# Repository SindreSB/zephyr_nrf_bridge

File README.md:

# Zephyr based bridge for Dexcom G4

Highly WIP, and not at all working

## Installation
This repo contains a west manifest file, which enables this to be a manifest repo when using the west tool.

Steps to get up and running:
1. Follow install guide for zephyr/west
1. Clone this repo 
1. Set the variables:
    * ZEPHYR_BASE=\<path to zephyr>
    * ZEPHYR_TOOLCHAIN_VARIANT=gnuarmemb
    * GNUARMEMB_TOOLCHAIN_PATH=\<path to gnu>
1. cd into the app directory
1. Use west build with the propper arguments and -s .
    * west build -b nrf52_pca10040 -s .

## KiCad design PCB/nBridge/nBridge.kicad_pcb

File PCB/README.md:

# nBridge PCB

The nBridge consists of a LiPo charger, a 3.3 regulator, a BL652 BLE module and a CC2500 module

## Versions
V1: Base design. Used very small parts which are too difficult to reliably solder
V2: Lower part count with larger components, as well as micro-USB instead of USB-C type connector.

## Parts list
The partslist is still changing, and it is easier to export it from the most recent desgin files than to have possibly outdatet information here. All passives are 0804 size componetns, while hte regulator and LDO are SOT23. The LEDs are 0603. 

## PCB 
The PCB can be found on https://aisler.net/p/FUKRPVUI. Newer, and maybe untested, revisions might be available there as well. The full source of the PCB is in the folder nBridge, though some symbols might be in different libraries not included. Currently, only revision 1 has been ordered.

## Pinout (V1)
### NRF52 - CC2500
| BL652 pin(V1) | nRF52832 pin | Function | 
|----|-|-----|
| 31 | P0.19 | CC2500 - MOSI | 
| 32 | P0.31 | CC2500 - CLK |
| 33 | P0.30 | CC2500 - MISO |
| 35 | P0.28 | CC2500 - GDO0 |
| 36 | P0.27 | CC2500 - GDO2 |
| 37 | P0.26 | CC2500 - CSn |
| 34 | P0.29/AIN5 | Analog input of battery voltage |
| 38 | P0.25 | Enable battery voltage measurement |
| 20 | P0.05 | LED0 |
| 19 | P0.06 | LED1 |
| 5  | SWDIO | SWDIO |
| 6  | SWDCLK | SWDCLK |
| 7  | P0.21 | nRST |
| 9  | P0.18 | SWO |

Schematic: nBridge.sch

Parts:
C1, C2, C3, C4: 1uF; C_0805_2012Metric
D1: GREEN LED; LED_0603_1608Metric
D2: RED LED; LED_0603_1608Metric
J1: 0473460001; USB_Micro_B_Female_0473460001; MPN 0473460001; Digi-Key_PN WM17141CT-ND
J2: Conn_01x06; Conn_Pas_01x06_1.27mm
J3: Conn_01x02; PinHeader_1x02_P2.54mm_Vertical
R1: 4k; R_0805_2012Metric
R4, R5: 220R; R_0805_2012Metric
R6: 27k; R_0805_2012Metric
R7: 10k; R_0805_2012Metric
SW1: Switch-SPDT; CSS-121XB
U1: LP5907MFX-3_3_NOPB; SOT-753; MPN LP5907MFX-3.3/NOPB; Digi-Key_PN 296-38557-1-ND
U2: MCP73812T-420I_OT; SOT-753; MPN MCP73812T-420I/OT; Digi-Key_PN MCP73812T-420I/OTCT-ND
U3: BL652; Laird_BL652
U4: CC2500Module

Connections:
+3V3: C3.1, J2.1, R4.1, R5.1, U1.5, U3.26 (VDD), U4.2 (3.3V)
/BAT_MSR: R6.2, R7.1, U3.34 (SIO_29/AIN5)
/BAT_MSR_EN: R7.2, U3.35 (SIO_28/AIN4)
/CLK: U3.32 (SIO_31/AIN7), U4.4 (CLK)
/GDO0: U3.29 (SIO_15), U4.7 (GDO0)
/GDO2: U3.30 (SIO_17), U4.6 (GDO2)
/LED0: D2.1 (K), U3.20 (SIO_05/AIN3)
/LED1: D1.1 (K), U3.19 (SIO_06)
/MISO: U3.31 (SIO_19), U4.5 (MISO)
/MOSI: U3.33 (SIO_30/AIN6), U4.3 (MOSI)
/SWDCLK: J2.4, U3.6 (SWDCLK)
/SWDIO: J2.5, U3.5 (SWDIO)
/SWO: J2.2, U3.9 (SIO_18)
/USB+: C2.1, J1.1, U2.1, U2.4
/V_BAT: C1.1, C4.1, J3.1, R6.1, SW1.2 (C), U1.1, U2.3
/nCS: U3.28 (SIO_13), U4.8 (~CS)
/nRESET: J2.3, U3.7 (SIO_21)
GND: C1.2, C2.2, C3.2, C4.2, J1.5, J1.SH, J2.6, J3.2, R1.2, SW1.1 (A), U1.2, U2.2, U3.1 (GND), U3.16 (GND), U3.27 (GND), U3.39 (GND), U4.1 (GND)
unnamed: D1.2 (A), R4.2
unnamed: D2.2 (A), R5.2
unnamed: R1.1, U2.5
unnamed: SW1.3 (B), U1.3

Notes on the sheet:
SWD interface
BATTERY CONNECTOR
STATUS LEDS
CC2500 MODULE

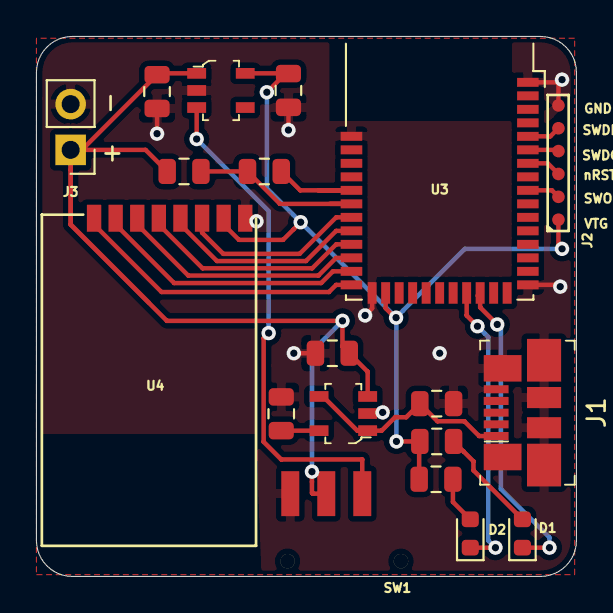
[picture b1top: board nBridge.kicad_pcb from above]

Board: 2 copper layers, 30.0 x 30.0 mm, 19 parts (0 on the bottom side), 22 nets.

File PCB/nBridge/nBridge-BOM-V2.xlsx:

Reference | Quantity | Value | Footprint | Digikey part number |  | Datasheet
C2 C4 C1 C3 | 4 | 1uF | Capacitor_SMD:C_0402_1005Metric | 1276-1067-1-ND |  | ~
D1 | 1 | LED | LED_SMD:LED_0603_1608Metric | 160-1447-1-ND |  | ~
D2 | 1 | LED | LED_SMD:LED_0603_1608Metric | 160-1446-1-ND
J1 | 1 | USB_C_Receptacle_USB2.0 | SharedFootprints:12401610E4#2A | 12401610E4#2ACT-ND |  | https://www.usb.org/sites/default/files/documents/usb_type-c.zip
J2 | 1 | Conn_01x06 | SharedFootprints:Conn_Pas_01x06_1.27mm | Do not buy |  | ~
J3 | 1 | Conn_01x02 | Connector_PinHeader_2.54mm:PinHeader_1x02_P2.54mm_Vertical | Do not buy |  | ~
R1 R7 | 2 | 10k | Resistor_SMD:R_0402_1005Metric | 1276-3530-1-ND |  | ~
R2 | 1 | 1k35 | Resistor_SMD:R_0402_1005Metric | P560AWDKR-ND | 560 instead of 1k35 gives 240mA IFAST | ~
R3 | 1 | 6k | Resistor_SMD:R_0402_1005Metric | P5.6KAWCT-ND | 5.6k instead of 6k | ~
R4 R5 | 2 | 220R | Resistor_SMD:R_0402_1005Metric | 541-4247-1-ND |  | ~
R6 | 1 | 27k | Resistor_SMD:R_0402_1005Metric | P27KAWCT-ND |  | ~
SW1 | 1 | Switch-SPDT | SharedFootprints:CSS-121XB | 563-1091-1-ND |  | ~
U1 | 1 | TPS7A0533PYKAR | SharedFootprints:TPS7A0533PYKAR | 296-52115-1-ND
U2 | 1 | BQ25100YFPR | SharedFootprints:BQ25100YFPR | 296-39931-1-ND
U3 | 1 | BL652 | RF_Module:Laird_BL652 | BL652-SA-01-CT-ND |  | http://cdn.lairdtech.com/home/brandworld/files/Datasheet%20-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
U4 | 1 | CC2500Module | nBridge:CC2500Module | Do not buy

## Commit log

2019-01-23 Add initial samples
2019-01-23 Add ignore of build files
2019-01-23 Updated cpp properties for VS Code
2019-01-29 Add working GPIO and SPI test, as well as CC2500 library
2019-01-30 Minor fixups
2019-01-30 Remove attempt to sample MISO
    Instead simply reading the status byte and checking that first bit is 0 after device has been sleeping or off should be sufficient
2019-01-31 Enable interrupts on GDO pins
2019-02-01 Massive changes to utilize a context instead of globals
2019-02-05 Working packet detection
2019-02-06 Update CC2500 config to be able to detect Dexcom packages
2019-02-07 Fix masking of marcstate register
2019-02-20 Add west manifest file
2019-02-20 Rename .yaml to .yml
2019-02-20 Update readme to include steps for for using this repo
2019-02-21 Remove west manifest and update readme to reflect simpler setup
2019-02-22 Replace printk with LOG_INF except for packet reception
2019-02-25 Implement basic conversion of values for testing purposes
2019-02-26 Refactor code in cc2500 spi
2019-02-26 Refactored and renamed source files
2019-02-27 Simplify cmake list and move code from cc-util to dex-utils
2019-02-27 Add CRC check and refactor value extraction
2019-02-28 Rewrite package handeling
2019-02-28 Use fifo to pass hand off received packages
2019-02-28 Refactor and rewrite into event based handeling
2019-02-28 Create macro for creating a receiver
2019-03-04 Refactor and change pacakge receiption timeouts
2019-03-04 First attempt at custom BT characteristic
2019-04-01 Add board definitions for both breakout and nBridge
2019-04-01 Add first attept for characteristic
2019-04-01 FIx board definition for n_bridge board
2019-04-01 Update config files
2019-04-02 Update readme and remove out of tree board from CMakeList
2019-04-06 Fixes to config, add initial CGM Service and record database
2019-04-08 Change timestamp on measurements to be deltas
2019-04-09 Start tracking PCB
2019-04-09 Update pinout to correspond to PCB
2019-04-10 Add DT overlay for nrf52840-mdk board
2019-04-10 Make pin configurations into kconfig options
2019-04-10 Update configs to new kconfig symbols
2019-04-10 Add simple float type representation of values and send timestamp even though time is not set
2019-04-10 Add conditional compilation based on kconfig CC2500 option and fix simulation
2019-04-19 Reorder data in measurement package
2019-04-21 Use kconfig option for simulated measurements
2019-04-21 Add xBridge2 protocol spesification
2019-04-21 Update xBridge2_Protocol.md
    Minor modifications to fix formating issues
2019-04-21 Begin implementing xBridge2 protocol instead of SimpleCGMS
2019-04-22 Enable sending all buffered measurements upon connection
2019-04-22 Set hard coded public address
2019-04-22 Fix conditional compile of simulated vs real receiver
2019-04-23 Remove RTC
2019-04-25 Rewrite hand off of package from CC2500 to use callback
2019-05-01 Make wakeup margin into a defined constant
2019-05-01 Simplify design, fewer and more easily solderable components
2019-05-01 Minor modifications
2019-05-02 Update part values and remove unused silkscreen
2019-05-03 Add 3d models to V2
2019-05-03 Add USB model
2019-05-03 Update PCB readme
